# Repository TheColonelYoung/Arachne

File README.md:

# Project Arachne  
Mainly 3D printed manipulator with 6 axis of freedom based on design of steward platform  

**!!! Now the notes in this repository are rather assumptions that will need to be verified in practice !!!**  

Platform is based on two nearly triangular bases connected with 6 linear actuators.  
Control of these actuators is driven from motherboard.  
Lower base is stationary, upper base part is movable.  
Motherboard is positioned in lower triangle base. Motherboard communicates with controller (pc) via serial line with G-code.  
First version of platform is 3D printed. Next version are supposed to be from aluminium.  

# **Motion system**  
Motion system is based on [affine transformation](https://en.wikipedia.org/wiki/Affine_transformation).  
Basic system contains from seven points. Which are placed in center of platform and in points of connection with actuators.  
Points are on both triangular bases. Corresponding points have same numbers.  
Position of point is described as coordinates in cartesian system.  
Center point is not used for calculation of motion, is used only as center point of mass.  
- Represent zero-point in three-dimensional space  
- Zero point of Z is when platform is set to minimal height (home position)  
- Can probably be used for optimization of speed  
- Center point can be used to determinate unreachable positions (not all) and as center position of object for affine transformations  

Every point is represented as vector [x,y,z,1].  

### Travel distance  
Distance between connect points &nbsp;of actuator on lower and upper bases is calculated.  
- Calculation is based on usage of euclidian distance calculation in three dimensional space  
- $d(a,b) = \sqrt{(a_x - b_x)^2 + (a_y - b_y)^2 + (a_z - b_z)^2}$  

Affine transformation is applied on all point of connection with actuators on upper base.  
Now is calculated new distance between fixed and movable points. Difference between distances in old and new position is travel distance of actuator.  
By repeating this process for every actuator is calculated one move of platform.  
Rotation terms: Pitch(X), Roll(Y), Yaw(Z)  

### Speed  
Speed scaling is linear based on travel distance of actuator.  
Acceleration must grow proportionally as speed.  
Traveled distance is integration of actual speed of motor by time.  
Example: Two motor M1 - travels 10mm, M2 - travels 30mm,  
- Maximal speed is tested (before usage of device) and used for motor with the longest distance (as well as acceleration)  
- M1 use three-times lower speed and acceleration because of travel distance is three-times lower  
- Travel time is same for both motor, so motors cannot jam due to incorrect position  

### Problems  
Jams of platforms are possible when movement is not synchronized. In this state some motor can be in end-position, but motion is not done.  
Main issue is when position of points in unknown. This happens when platform is powered on. Before power of platform must be homed -> this cannot be reliably secured.  
Possible homing sequence is that all actuators will be moved with same speed to their home position. But there is possibility of jam.  

### Example  
This example is calculated only for one actuators, others have same calculations.  
Platform is now at home position. So position of points describes offset from zero point.  
Length of all actuator is same. Probably zero length of pushrods + length of body.  
In this example is body length two times retractable length. Minimal length 30mm, maximal length is 50mm.  
Length is calculated between mates connecting base and actuator.  

Point on upper base ($P_{UP}$) is at `[-2, 0, 0, 1]`, motions are shift forward (Y+2), and rotation to right(Z+90°).  
Point on lower base ($P_{LOW}$) is at `[-1, 2, -2.45, 1]`, Z offset is determinated by vertical distance between lower and upper base in home state.  

**Shift matrix:**  
$\begin{bmatrix}1 & 0 & 0 & X \\0 & 1 & 0 & Y \\ 0 & 0 & 1 & Z \\ 0 & 0 & 0 & 1 \\\end{bmatrix}$  

**Rotation matrix around Z - Yaw($\gamma$):**  
$\begin{bmatrix}\cos(\gamma) & -\sin(\gamma) & 0 & 0 \\\sin(\gamma) & \cos(\gamma) & 0 & 0 \\ 0 & 0 & 1 & 0 \\ 0 & 0 & 0 & 1 \\\end{bmatrix}$  

**Multiplication of matrix**  
Note: if platform is not home is necessary to make another translation of object from current position of center point to center of space. This is represented as empty translation-1 matrix  
[Translation-1 * Rotation * Translation * Point]  

New coordinates of $P_{UP}$ are `[-2, -2, 0, 1]`  

Old distance between $P_{UP}$ and $P_{LOW}$ is: 3.317 cm  
- Calculation: $d = \sqrt{(-2 - -1)^2 + (0 - 2)^2 + (0 - -2.45)^2} = 3.317$  

New distance between $P_{UP}$ and $P_{LOW}$ is: 4.796 cm  
- Calculation: $d = \sqrt{(-2 - -1)^2 + (-2 - 2)^2 + (0 - -2.45)^2} = 4.796$  

Difference between old and new length of actuator is: 1.479 cm  

So actuator must change length to 4.796 cm, which is nearly maximal length (in this example).  
Change of length is + 1.479 cm, speed and acceleration depends on motion of other actuators.  

# **Construction**  

### Joints  
Linear actuators are connected with hexagonal platform with universal joint with can give joint freedom to move freely. Rotation of joint should not be constrained by joint but by length of arm (linear actuator length).  

Joints consists of 3 parts. Two forks and one central block. X and Y axis of forks are perpendicular between forks (forks are turned against self by 90° on Z axis). Fork is connected to central block through small ball bearing. This ball bearing removed as much of friction as possible.  

**Universal joint**  

# **PCB**  
Main Motherboard contains six stepper motor drivers L6470 in TSSOP28 package.  
PCB is designed with maximal dimensions of 10x7cm, so it can be cheaply manufactured.  

### Specifications  
- Maximal input voltage is 36V  
- PCB is designed for maximal current of 8A into motor, this assumes 6x1.2A stepper motors  
- Input stage contains current sensor for monitoring of actual current  
- Stepper motor end position can be detected via driver build-in stall detection or through endstop (one per each stepper)  
    - Endstop should be Normally Open and connect ground to sense pin  
    - Connector contains 3.3V power output for powering some position sensor instead of tactile switch between sense and ground  
- Stepper drivers are in line, so heatsinks can be fit on them  
- Via EXT IDC connector can be connected sensor for motion feedback over SPI or I2C  
- DEBUG connector pinout is compatible with 10-pin IDC Saleae layout  
- Minimal width trace is 5.1 mils (0.13 mm)  
- Minimal drill size id 0.3mm

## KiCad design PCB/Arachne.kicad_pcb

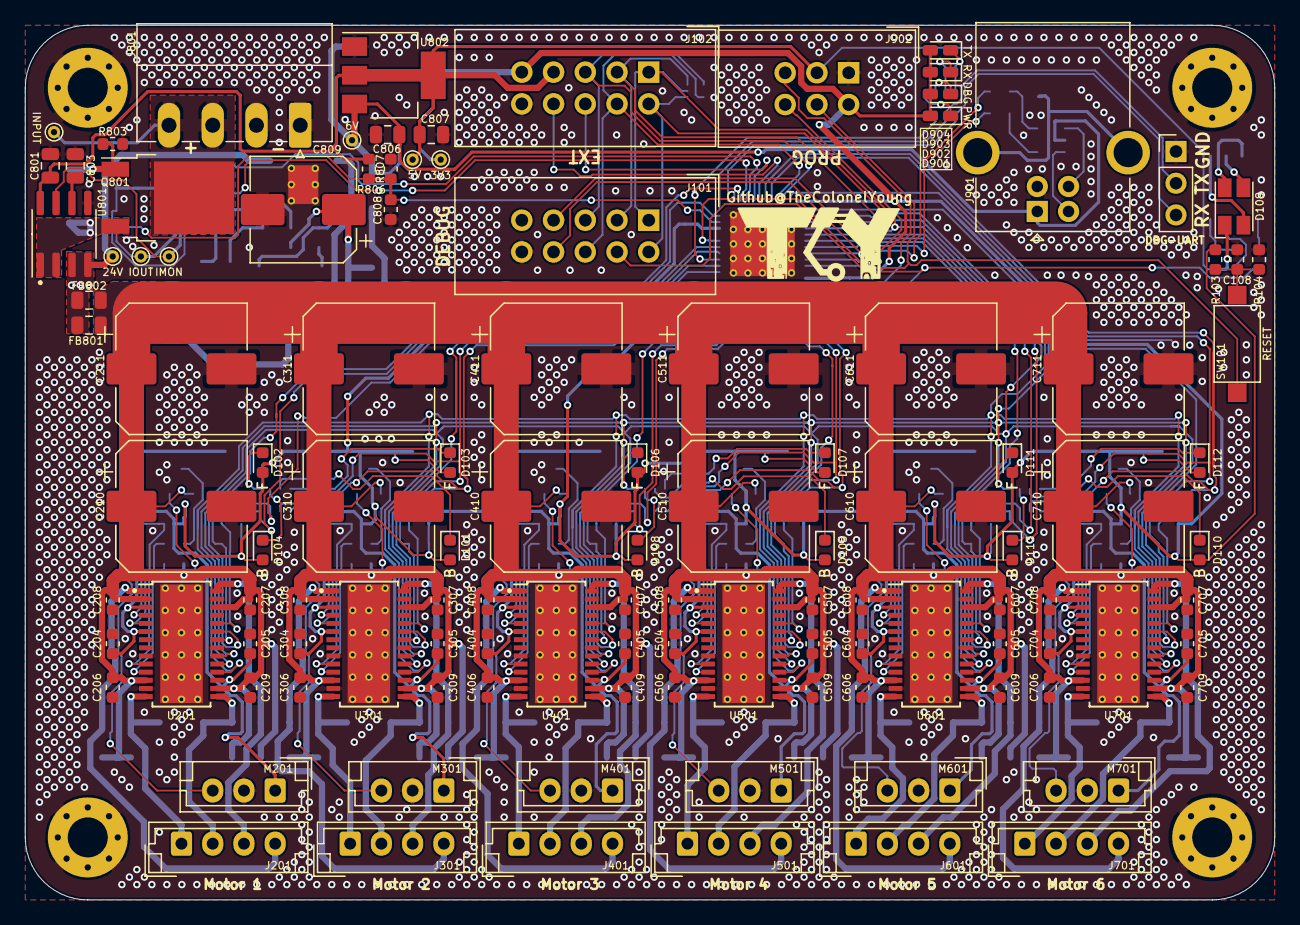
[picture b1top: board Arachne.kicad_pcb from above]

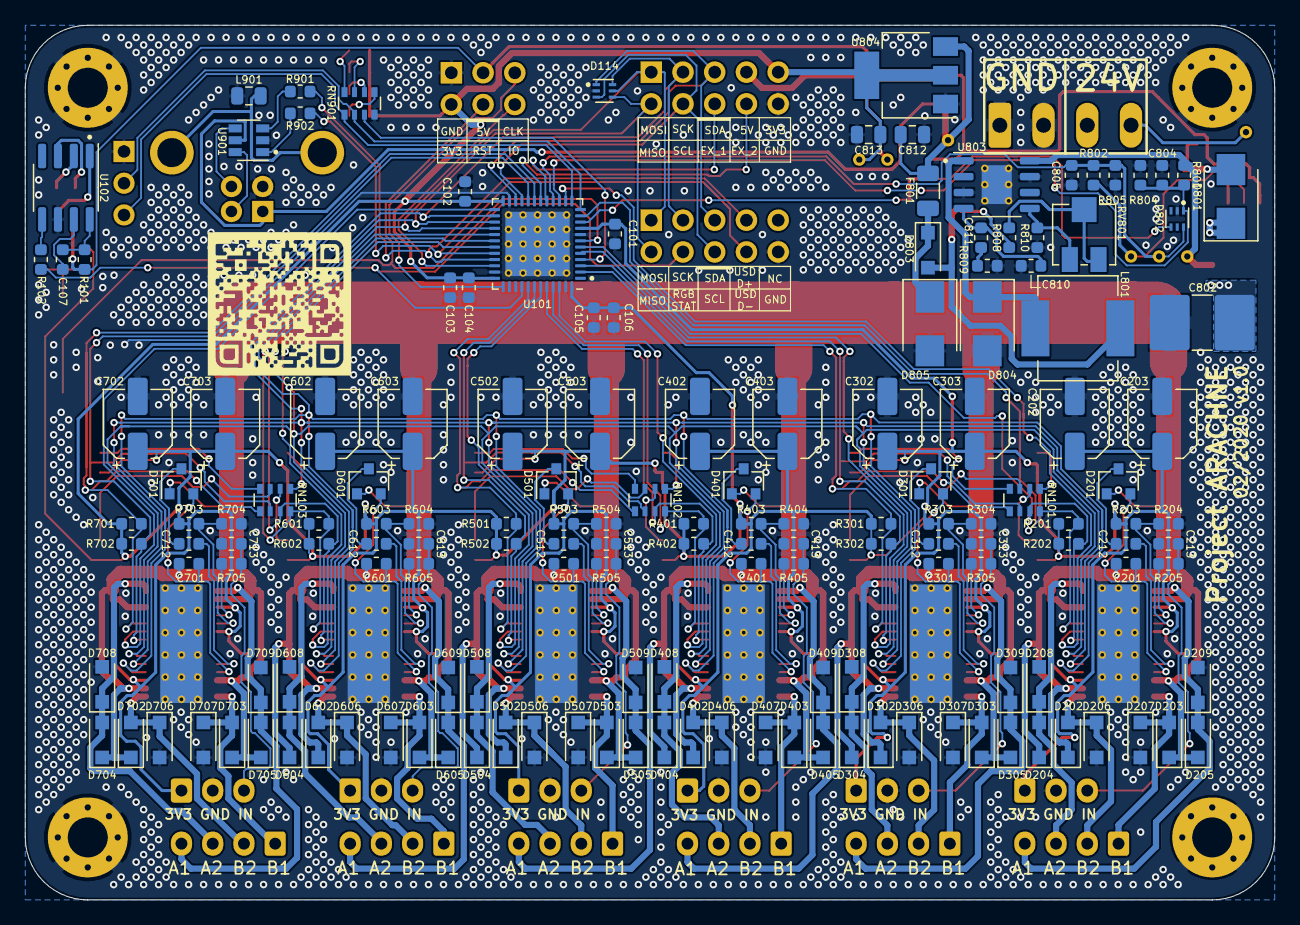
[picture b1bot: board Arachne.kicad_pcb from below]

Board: 2 copper layers, 100.0 x 70.0 mm, 276 parts (158 on the bottom side), 143 nets.

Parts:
C101, C102, C103, C104, C105, C106, C107, C108, C213, C313, C413, C513, C613, C713, C804, C805, C808: 100nF; C_0603_1608Metric
C201, C301, C401, C501, C601, C701: 220nF/16V; C_0603_1608Metric
C202, C203, C302, C303, C402, C403, C502, C503, C602, C603, C702, C703: 47uF/6,3V; CP_Elec_5x5.3
C204, C205, C206, C207, C208, C209, C304, C305, C306, C307, C308, C309, C404, C405, C406, C407, C408, C409, C504, C505, C506, C507, C508, C509, C604, C605, C606, C607, C608, C609, C704, C705, C706, C707, C708, C709: 100nF/50V; C_0603_1608Metric
C210, C211, C310, C311, C410, C411, C510, C511, C610, C611, C710, C711: 100uF/63V; CP_Elec_10x10
C212, C312, C412, C512, C612, C712: 10nF/50V; C_0603_1608Metric
C801, C803: 1uF (X7R); C_0805_2012Metric
C802: 10uF 50V (ceramic); C_2816_7142Metric_Pad3.20x4.45mm_HandSolder
C806, C807, C812, C813: 4.7uF (X7R); C_0805_2012Metric
C809: 300uF 16V; CP_Elec_8x10
C810: 220nF; C_0603_1608Metric
C811: 22nF; C_0603_1608Metric
D101, D102, D103, D104, D105, D106, D107, D108, D110, D111, D112, D113: LED; LED_0603_1608Metric
D109: ASMB-MTB0-0A3A2; LED_Avago_PLCC4_3.2x2.8mm_CW
D114, D802: ESDA6V1-5SC6; ST_UQFN-6L_1.5x1.7mm_Pitch0.5mm
D201, D301, D401, D501, D601, D701: BAV99; SOT-23
D202, D203, D204, D205, D206, D207, D208, D209, D302, D303, D304, D305, D306, D307, D308, D309, D402, D403, D404, D405, D406, D407, D408, D409, D502, D503, D504, D505, D506, D507, D508, D509, D602, D603, D604, D605, D606, D607, D608, D609, D702, D703, D704, D705, D706, D707, D708, D709, D803: SKL310; D_SOD-123F
D801: 1SMB5925; D_SMB
D804: 7V; D_SMB
D805: STPS340U; D_SMB
D901: GREEN; LED_0603_1608Metric_Castellated
D902: YELLOW; LED_0603_1608Metric_Castellated
D903, D904: BLUE; LED_0603_1608Metric_Castellated
F801: 2A; Fuse_1206_3216Metric
FB801, FB802: 22R@100MHz; L_0805_2012Metric
H101, H102, H103, H104: M3; MountingHole_3.2mm_M3_Pad_Via
J101: Salae_logic; IDC-Header_2x05_P2.54mm_Vertical
J102: Extension; IDC-Header_2x05_P2.54mm_Vertical
J201, J301, J401, J501, J601, J701: SW2; JST_EH_B3B-EH-A_1x03_P2.50mm_Vertical
J801: V_IN; PhoenixContact_MC_1,5_4-G-3.5_1x04_P3.50mm_Horizontal
J901: USB_B; USB_B_OST_USB-B1HSxx_Horizontal
J902: PROG_CONN_STM_6p; IDC-Header_2x03_P2.54mm_Vertical
J903: DBG_UART; PinHeader_1x03_P2.54mm_Vertical
L801: 15uH; L_Neosid_Ms85
L901: 50R@100MHz, 3A; L_0805_2012Metric
M201, M301, M401, M501, M601, M701: Stepper_Motor_bipolar; JST_EH_B4B-EH-A_1x04_P2.50mm_Vertical
Q801: AOD4189; TO-252-2
R101, R102, R901, R902: 22R; R_0603_1608Metric
R103, R201, R202, R301, R302, R401, R402, R501, R502, R601, R602, R701, R702, R803: 100k; R_0603_1608Metric
R104, R802, R804, R805, R806, R807, R810: 10k; R_0603_1608Metric
R203, R303, R403, R503, R603, R703: 560k; R_0603_1608Metric
R204, R304, R404, R504, R604, R704: 2k7; R_0603_1608Metric
R205, R305, R405, R505, R605, R705: 1k; R_0603_1608Metric
R801: 180k; R_0603_1608Metric
R808: 20k; R_0603_1608Metric
R809: 4.7k; R_0603_1608Metric
RN101, RN102, RN103: 4x22R; R_Array_Convex_4x0603
RN901: R_Pack04; R_Array_Convex_4x0603
RV801: 20k; Potentiometer_Bourns_3214J_Horizontal
SW101: SW_Push; SW_SPST_CK_RS282G05A3
TP801: PWR_IN; TestPoint_THTPad_D1.0mm_Drill0.5mm
TP803: I_MAIN; TestPoint_THTPad_D1.0mm_Drill0.5mm
TP804: 24V; TestPoint_THTPad_D1.0mm_Drill0.5mm
TP805: I_DIV; TestPoint_THTPad_D1.0mm_Drill0.5mm
TP806: 5V; TestPoint_THTPad_D1.0mm_Drill0.5mm
TP807: 6V; TestPoint_THTPad_D1.0mm_Drill0.5mm
TP808: 3V3; TestPoint_THTPad_D1.0mm_Drill0.5mm
U101: STM32L452CEUx; QFN-48-1EP_7x7mm_P0.5mm_EP5.15x5.15mm_ThermalVias
U102: WS2818B; SOP-8_3.76x4.96mm_P1.27mm
U201, U301, U401, U501, U601, U701: L6470_HTSSOP28; HTSSOP-28-1EP_4.4x9.7mm_P0.65mm_EP3.4x9.5mm_ThermalVias
U801: ACS712xLCTR-20A; SOIC-8_3.9x4.9mm_P1.27mm
U802: NCP1117-5.0_SOT223; SOT-223-3_TabPin2
U803: L5973D; HSOP-8-1EP_3.9x4.9mm_P1.27mm_EP2.41x3.1mm_ThermalVias
U804: NCP1117-3.3_SOT223; SOT-223-3_TabPin2
U901: USBLC6-2SC6; SOT-23-6

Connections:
+3V3: C101.1, C102.1, C103.1, C104.1, C105.1, C106.1, C202.1, C203.1, C204.1, C205.1, C302.1, C303.1, C304.1, C305.1, C402.1, C403.1, C404.1, C405.1, C502.1, C503.1, C504.1, C505.1, C602.1, C603.1, C604.1, C605.1, C702.1, C703.1, C704.1, C705.1, C813.1, D101.2, D102.2, D103.2, D104.2, D105.2, D106.2, D107.2, D108.2, D110.2, D111.2, D112.2, D113.2, D901.2, D902.2, D903.2, D904.2, J102.9, J201.1, J301.1, J401.1, J501.1, J601.1, J701.1, J902.2, R103.1, R201.1, R202.1, R203.1, R301.1, R302.1, R303.1, R401.1, R402.1, R403.1, R501.1, R502.1, R503.1, R601.1, R602.1, R603.1, R701.1, R702.1, R703.1, TP808.1, U101.9, U101.24, U101.36, U101.48, U201.3, U201.6, U201.17, U301.3, U301.6, U301.17, U401.3, U401.6, U401.17, U501.3, U501.6, U501.17, U601.3, U601.6, U601.17, U701.3, U701.6, U701.17, U804.2
+5V: C801.2, C807.1, D109.1, J102.7, J902.3, R101.1, R806.1, TP806.1, U801.8, U802.2
+24V: C802.1, FB801.2, FB802.2, R801.1, TP804.1, U801.3, U801.4, U803.8
/5V_MON: C808.1, D802.4, R806.2, R807.1, U101.10
/BUSY_1: R202.2, RN101.7, U101.6, U201.22
/BUSY_2: R302.2, RN101.6, U101.3, U301.22
/BUSY_3: R402.2, RN102.7, U101.44, U401.22
/BUSY_4: R502.2, RN102.6, U101.42, U501.22
/BUSY_5: R602.2, RN103.7, U101.30, U601.22
/BUSY_6: R702.2, RN103.6, U101.20, U701.22
/CS_1: U101.14, U201.23
/CS_2: U101.5, U301.23
/CS_3: U101.46, U401.23
/CS_4: U101.43, U501.23
/CS_5: U101.31, U601.23
/CS_6: U101.25, U701.23
/EXT_1: J102.6, U101.17
/EXT_2: J102.8, U101.18
/FLAG_1: R201.2, RN101.8, U101.11, U201.24
/FLAG_2: R301.2, RN101.5, U101.2, U301.24
/FLAG_3: R401.2, RN102.8, U101.45, U401.24
/FLAG_4: R501.2, RN102.5, U101.41, U501.24
/FLAG_5: R601.2, RN103.8, U101.29, U601.24
/FLAG_6: R701.2, RN103.5, U101.19, U701.24
/I2C_SCL: D114.3, J101.6, J102.4, U101.21
/I2C_SDA: D114.1, J101.5, J102.5, U101.22
/I_MON: C805.1, D802.6, R802.2, R805.1, TP805.1, U101.16
/Interface/D+: R901.2, U901.3
/Interface/D-: R902.2, U901.1
/Interface/USB+: J901.3, U901.4
/Interface/USB-: J901.2, U901.6
/Motor_1/SW: R205.2, U201.4
/Motor_2/SW: R305.2, U301.4
/Motor_3/SW: R405.2, U401.4
/Motor_4/SW: R505.2, U501.4
/Motor_5/SW: R605.2, U601.4
/Motor_6/SW: R705.2, U701.4
/PWR_MON: C804.1, D802.1, R801.2, R804.1, U101.15
/RESET: J902.4, SW101.2, U101.7
/RGB_STAT: J101.4, R102.2, U101.40
/SPI_MISO: D114.4, J101.2, J102.2, U101.27, U201.18, U301.18, U401.18, U501.18, U601.18, U701.18
/SPI_MOSI: D114.5, J101.1, J102.1, U101.28, U201.20, U301.20, U401.20, U501.20, U601.20, U701.20
/SPI_SCK: D114.6, J101.3, J102.3, U101.26, U201.19, U301.19, U401.19, U501.19, U601.19, U701.19
/STAT: RN901.7, U101.4
/SWCLK: J902.5, U101.37
/SWDIO: J902.6, U101.34
/UART_2_RX: J903.3, RN901.5, U101.13
/UART_2_TX: J903.2, RN901.6, U101.12
/USB_D+: J101.7, R901.1, U101.33
/USB_D-: J101.8, R902.1, U101.32
GND: C101.2, C102.2, C103.2, C104.2, C105.2, C106.2, C108.2, C202.2, C203.2, C204.2, C205.2, C206.2, C207.2, C208.2, C209.2, C210.2, C211.2, C213.2, C302.2, C303.2, C304.2, C305.2, C306.2, C307.2, C308.2, C309.2, C310.2, C311.2, C313.2, C402.2, C403.2, C404.2, C405.2, C406.2, C407.2, C408.2, C409.2, C410.2, C411.2, C413.2, C502.2, C503.2, C504.2, C505.2, C506.2, C507.2, C508.2, C509.2, C510.2, C511.2, C513.2, C602.2, C603.2, C604.2, C605.2, C606.2, C607.2, C608.2, C609.2, C610.2, C611.2, C613.2, C702.2, C703.2, C704.2, C705.2, C706.2, C707.2, C708.2, C709.2, C710.2, C711.2, C713.2, C801.1, C802.2, C803.2, C804.2, C805.2, C806.2, C807.2, C808.2, C809.2, C810.2, C812.2, C813.2, D114.2, D206.2, D207.2, D208.2, D209.2, D306.2, D307.2, D308.2, D309.2, D406.2, D407.2, D408.2, D409.2, D506.2, D507.2, D508.2, D509.2, D606.2, D607.2, D608.2, D609.2, D706.2, D707.2, D708.2, D709.2, D802.2, D804.2, D805.2, H101.1, H102.1, H103.1, H104.1, J101.10, J102.10, J201.2, J301.2, J401.2, J501.2, J601.2, J701.2, J801.1, J801.2, J901.4, J902.1, J903.1, L901.2, R104.2, R204.2, R304.2, R404.2, R504.2, R604.2, R704.2, R803.2, R804.2, R805.2, R807.2, R809.2, R810.2, RN901.8, U101.8, U101.23, U101.35, U101.47, U101.49, U102.6, U201.9, U201.13, U201.21, U201.27, U201.29, U301.9, U301.13, U301.21, U301.27, U301.29, U401.9, U401.13, U401.21, U401.27, U401.29, U501.9, U501.13, U501.21, U501.27, U501.29, U601.9, U601.13, U601.21, U601.27, U601.29, U701.9, U701.13, U701.21, U701.27, U701.29, U801.5, U802.1, U803.3, U803.7, U803.9, U804.1, U901.2
unnamed: C107.1, R101.2, U102.8
unnamed: C107.2, U102.7
unnamed: C108.1, R103.2, R104.1, SW101.1
unnamed: C201.1, D201.2, U201.11
unnamed: C212.1, D201.3
unnamed: C212.2, U201.10
unnamed: C213.1, J201.3, R205.1
unnamed: C301.1, D301.2, U301.11
unnamed: C312.1, D301.3
unnamed: C312.2, U301.10
unnamed: C313.1, J301.3, R305.1
unnamed: C401.1, D401.2, U401.11
unnamed: C412.1, D401.3
unnamed: C412.2, U401.10
unnamed: C413.1, J401.3, R405.1
unnamed: C501.1, D501.2, U501.11
unnamed: C512.1, D501.3
unnamed: C512.2, U501.10
unnamed: C513.1, J501.3, R505.1
unnamed: C601.1, D601.2, U601.11
unnamed: C612.1, D601.3
unnamed: C612.2, U601.10
unnamed: C613.1, J601.3, R605.1
unnamed: C701.1, D701.2, U701.11
unnamed: C712.1, D701.3
unnamed: C712.2, U701.10
unnamed: C713.1, J701.3, R705.1
unnamed: C803.1, U801.6
unnamed: C809.1, D803.2, L801.2, R808.1
unnamed: C810.1, C811.1, U803.4
unnamed: C811.2, R809.1
unnamed: D101.1, RN101.3
unnamed: D102.1, RN101.1
unnamed: D103.1, RN101.4
unnamed: D104.1, RN101.2
unnamed: D105.1, RN102.3
unnamed: D106.1, RN102.1
unnamed: D107.1, RN102.4
unnamed: D108.1, RN102.2
unnamed: D109.2, U102.3
unnamed: D109.3, U102.2
unnamed: D109.4, U102.1
unnamed: D110.1, RN103.3
unnamed: D111.1, RN103.1
unnamed: D112.1, RN103.4
unnamed: D113.1, RN103.2
unnamed: D202.2, D206.1, M201.2, U201.15
unnamed: D203.2, D207.1, M201.1, U201.14
unnamed: D204.2, D208.1, M201.3, U201.28
unnamed: D205.2, D209.1, M201.4, U201.1
unnamed: D302.2, D306.1, M301.2, U301.15
unnamed: D303.2, D307.1, M301.1, U301.14
unnamed: D304.2, D308.1, M301.3, U301.28
unnamed: D305.2, D309.1, M301.4, U301.1
unnamed: D402.2, D406.1, M401.2, U401.15
unnamed: D403.2, D407.1, M401.1, U401.14
unnamed: D404.2, D408.1, M401.3, U401.28
unnamed: D405.2, D409.1, M401.4, U401.1
unnamed: D502.2, D506.1, M501.2, U501.15
unnamed: D503.2, D507.1, M501.1, U501.14
unnamed: D504.2, D508.1, M501.3, U501.28
unnamed: D505.2, D509.1, M501.4, U501.1
unnamed: D602.2, D606.1, M601.2, U601.15
unnamed: D603.2, D607.1, M601.1, U601.14
unnamed: D604.2, D608.1, M601.3, U601.28
unnamed: D605.2, D609.1, M601.4, U601.1
unnamed: D702.2, D706.1, M701.2, U701.15
unnamed: D703.2, D707.1, M701.1, U701.14
unnamed: D704.2, D708.1, M701.3, U701.28
unnamed: D705.2, D709.1, M701.4, U701.1
unnamed: D801.1, Q801.3, U801.1, U801.2
unnamed: D801.2, Q801.1, R803.1
unnamed: D803.1, D804.1, F801.2
unnamed: D805.1, L801.1, U803.1
unnamed: D901.1, RN901.1
unnamed: D902.1, RN901.2
unnamed: D903.1, RN901.3
unnamed: D904.1, RN901.4
unnamed: J801.3, J801.4, Q801.2, TP801.1
unnamed: J901.5, L901.1
unnamed: R102.1, U102.5
unnamed: R203.2, R204.1, U201.5
unnamed: R303.2, R304.1, U301.5
unnamed: R403.2, R404.1, U401.5
unnamed: R503.2, R504.1, U501.5
unnamed: R603.2, R604.1, U601.5
unnamed: R703.2, R704.1, U701.5
unnamed: R802.1, TP803.1, U801.7
unnamed: R808.2, RV801.1, RV801.2
unnamed: R810.1, RV801.3, U803.5
USB_VCC: C806.1, C812.1, F801.1, J901.1, TP807.1, U802.3, U804.3, U901.5
VMOT: C201.2, C206.1, C207.1, C208.1, C209.1, C210.1, C211.1, C301.2, C306.1, C307.1, C308.1, C309.1, C310.1, C311.1, C401.2, C406.1, C407.1, C408.1, C409.1, C410.1, C411.1, C501.2, C506.1, C507.1, C508.1, C509.1, C510.1, C511.1, C601.2, C606.1, C607.1, C608.1, C609.1, C610.1, C611.1, C701.2, C706.1, C707.1, C708.1, C709.1, C710.1, C711.1, D201.1, D202.1, D203.1, D204.1, D205.1, D301.1, D302.1, D303.1, D304.1, D305.1, D401.1, D402.1, D403.1, D404.1, D405.1, D501.1, D502.1, D503.1, D504.1, D505.1, D601.1, D602.1, D603.1, D604.1, D605.1, D701.1, D702.1, D703.1, D704.1, D705.1, FB801.1, FB802.1, U201.2, U201.12, U201.16, U201.26, U301.2, U301.12, U301.16, U301.26, U401.2, U401.12, U401.16, U401.26, U501.2, U501.12, U501.16, U501.26, U601.2, U601.12, U601.16, U601.26, U701.2, U701.12, U701.16, U701.26

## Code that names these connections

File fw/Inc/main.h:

/* USER CODE BEGIN Header */
/**
  ******************************************************************************
  * @file           : main.h
  * @brief          : Header for main.c file.
  *                   This file contains the common defines of the application.
  ******************************************************************************
  * @attention
  *
  * <h2><center>&copy; Copyright (c) 2020 STMicroelectronics.
  * All rights reserved.</center></h2>
  *
  * This software component is licensed by ST under BSD 3-Clause license,
  * the "License"; You may not use this file except in compliance with the
  * License. You may obtain a copy of the License at:
  *                        opensource.org/licenses/BSD-3-Clause
  *
  ******************************************************************************
  */
/* USER CODE END Header */

/* Define to prevent recursive inclusion -------------------------------------*/
#ifndef __MAIN_H
#define __MAIN_H

#ifdef __cplusplus
extern "C" {
#endif

/* Includes ------------------------------------------------------------------*/
#include "stm32l4xx_hal.h"

/* Private includes ----------------------------------------------------------*/
/* USER CODE BEGIN Includes */

/* USER CODE END Includes */

/* Exported types ------------------------------------------------------------*/
/* USER CODE BEGIN ET */
void SystemClock_Config(void);
/* USER CODE END ET */

/* Exported constants --------------------------------------------------------*/
/* USER CODE BEGIN EC */

/* USER CODE END EC */

/* Exported macro ------------------------------------------------------------*/
/* USER CODE BEGIN EM */

/* USER CODE END EM */

void HAL_TIM_MspPostInit(TIM_HandleTypeDef *htim);

/* Exported functions prototypes ---------------------------------------------*/
void Error_Handler(void);

/* USER CODE BEGIN EFP */

/* USER CODE END EFP */

/* Private defines -----------------------------------------------------------*/
#define FLAG_2_Pin GPIO_PIN_13
#define FLAG_2_GPIO_Port GPIOC
#define BUSY_2_Pin GPIO_PIN_14
#define BUSY_2_GPIO_Port GPIOC
#define STAT_Pin GPIO_PIN_15
#define STAT_GPIO_Port GPIOC
#define CS_2_Pin GPIO_PIN_0
#define CS_2_GPIO_Port GPIOH
#define BUSY_1_Pin GPIO_PIN_1
#define BUSY_1_GPIO_Port GPIOH
#define BUSY_1_EXTI_IRQn EXTI1_IRQn
#define _5V_MON_Pin GPIO_PIN_0
#define _5V_MON_GPIO_Port GPIOA
#define FLAG_1_Pin GPIO_PIN_1
#define FLAG_1_GPIO_Port GPIOA
#define CS_1_Pin GPIO_PIN_4
#define CS_1_GPIO_Port GPIOA
#define PWM_MON_Pin GPIO_PIN_5
#define PWM_MON_GPIO_Port GPIOA
#define I_MON_Pin GPIO_PIN_6
#define I_MON_GPIO_Port GPIOA
#define EXT_1_Pin GPIO_PIN_7
#define EXT_1_GPIO_Port GPIOA
#define EXT_2_Pin GPIO_PIN_0
#define EXT_2_GPIO_Port GPIOB
#define FLAG_6_Pin GPIO_PIN_1
#define FLAG_6_GPIO_Port GPIOB
#define BUSY_6_Pin GPIO_PIN_2
#define BUSY_6_GPIO_Port GPIOB
#define CS_6_Pin GPIO_PIN_12
#define CS_6_GPIO_Port GPIOB
#define FLAG_5_Pin GPIO_PIN_8
#define FLAG_5_GPIO_Port GPIOA
#define BUSY_5_Pin GPIO_PIN_9
#define BUSY_5_GPIO_Port GPIOA
#define CS_5_Pin GPIO_PIN_10
#define CS_5_GPIO_Port GPIOA
#define RGB_STAT_Pin GPIO_PIN_4
#define RGB_STAT_GPIO_Port GPIOB
#define FLAG_4_Pin GPIO_PIN_5
#define FLAG_4_GPIO_Port GPIOB
#define BUSY_4_Pin GPIO_PIN_6
#define BUSY_4_GPIO_Port GPIOB
#define CS_4_Pin GPIO_PIN_7
#define CS_4_GPIO_Port GPIOB
#define BUSY_3_Pin GPIO_PIN_3
#define BUSY_3_GPIO_Port GPIOH
#define FLAG_3_Pin GPIO_PIN_8
#define FLAG_3_GPIO_Port GPIOB
#define CS_3_Pin GPIO_PIN_9
#define CS_3_GPIO_Port GPIOB
/* USER CODE BEGIN Private defines */

/* USER CODE END Private defines */

#ifdef __cplusplus
}
#endif

#endif /* __MAIN_H */

/************************ (C) COPYRIGHT STMicroelectronics *****END OF FILE****/

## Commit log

2019-07-16 Initialization of Kicad project, update of description
2019-07-17 Notes: add notes about motion system and motion calculations
2019-07-17 Notes: add begin of example
2019-07-17 Notes: Example completion
2019-07-18 Notes: test of github latex web rendering, fixed typos, add translation-1 matrix
2019-07-18 Notes: add matrix rendered to picture into README.md
2019-07-18 Notes: equation rendering removed
2019-07-27 PCB-Schema: Initialization of project
    First sketch of power input and motor driver IC.
2019-07-27 PCB-Schema: Update of labels in power input
2019-08-05 Schema: add other motors and create SPI connection
2019-08-05 Notes: create PCB section with specifications
2019-11-08 img: add image of universal joint
2019-11-08 Notes: add part about connection of arm to platform (universal joint)
2020-02-04 Notes: image of Onshape assembly add to notes
2020-02-04 Add gitignore for bak files generated by Kicad
2020-02-04 STL: add universal joint for lower side of platform which connects to gearbox of arm
2020-02-04 STL: add upper universal joint parts
2020-02-04 Schema: add Interface schema, remove old mcu, add divider to current measuring
2020-02-04 Schema: add mcu, RGB LED signalization, reset circuit
2020-02-04 project cleanup, update gitignore, remove cache and rescue files
2020-02-04 Schema: add FLAG and BUSY LED signalization, fix driver ground connection
2020-02-04 Schema: new part annotation, package assignment
2020-02-05 PCB: create basic PB layout, add netlist
2020-02-05 PCB: component sorting, add driver space marks to comment layer
2020-02-06 PCB: routing of first part of stepper motor driver
2020-02-09 PCB: driver layout optimization, connect caps, connect endstop
2020-02-09 Schema: fix schema ERC, connect CS, FLAG and BUSY pins to MCU, connect SPI
    ERC: fixed L6470 pin types, add power flags, fixed programming
    connector pin types
2020-02-09 PCB: route CS track of 6th driver, optimize layout of driver, connect GND
2020-02-09 PCB: position labels in silkscreen for driver 6
2020-02-09 PCB: route driver number 5 (layout replication of 6 with modifications)
2020-02-10 PCB: add routing of remaining driver (1-4)
2020-02-10 Schema&PCB: shrink board to 80x100mm, remove excessive mounting holes
2020-02-10 Schema: swap resistor net input for FLAG and BUSY signalization
2020-02-10 PCB: route bus between drivers, place resistor nets
2020-02-10 PCB: update VMOT traces to 1 class wider variant
2020-02-10 PCB: route current meter, reverse polarity protection, stepdown converter
2020-02-11 PCB:
2020-02-11 PCB: upgrade power lines for VMOT (3mm -> 5mm), add second ferrite to VMOT
2020-02-12 PCB: create new layout for power supply, route LED signalization and reset
2020-02-12 PCB: routing of linear regulators, enhance ground connection (power supply)
2020-02-12 Schema: add Salae debug IDC connector
2020-02-12 PCB: change programing and debugging IDC connectors to vertical version
2020-02-12 PCB: change package size of USB ferrite from 1206 to 0803
2020-02-25 FW: project initialization, I/O pin setup
2020-02-25 FW: add I2C setup in CubeMX
2020-02-25 Schema: Swap pins for L6470 control on MCU
2020-02-26 Schema & PCB: add routing of MCu connection, debug and extension port
2020-02-26 FW: add pins to CubeMX for I2C and extension connector
2020-02-26 PCB: add ground via stitching, fix unconnected items
2020-02-26 PCB: add info labels to silkscreen
2020-03-01 project: add gerbers/ folder to gitignore
2020-03-01 PCB: fix labels for IDC connectors, add polarity signs to main power conn
2020-03-02 PCB: add labels to BUSY and FLAG LED of stepper motor drivers
2020-03-02 img: add render of arachne motherboard from KiCAD
2020-03-02 Notes: add image of motherboard to notes, move whole arachne picture to img/ folder
2020-03-02 PCB: fix rotation of connector labels
2020-03-08 PCB: change minimal drill size to 0.3mm (original was 0.2)
2020-03-09 Notes: update PCB description
2021-01-14 FW: project cleanup
2021-01-14 fixup! FW: project cleanup
2021-01-14 PCB: update project to kicad nightly 5.99
2021-01-15 Errata: errors description for v1.0
2021-05-11 FW: remove build folder from git
2021-05-11 fw: add USB middleware
2021-05-11 FW: enable SPI for L6470 and Timer_3 for WS2818
2021-05-11 FW: add communication with motor, logging and LED signaling
2021-06-25 project: migration to FreeRTOS
2021-06-25 Application: integration of eyrina G-code parser and FreeRTOS into device
2021-06-28 app: remove unused runout protection
